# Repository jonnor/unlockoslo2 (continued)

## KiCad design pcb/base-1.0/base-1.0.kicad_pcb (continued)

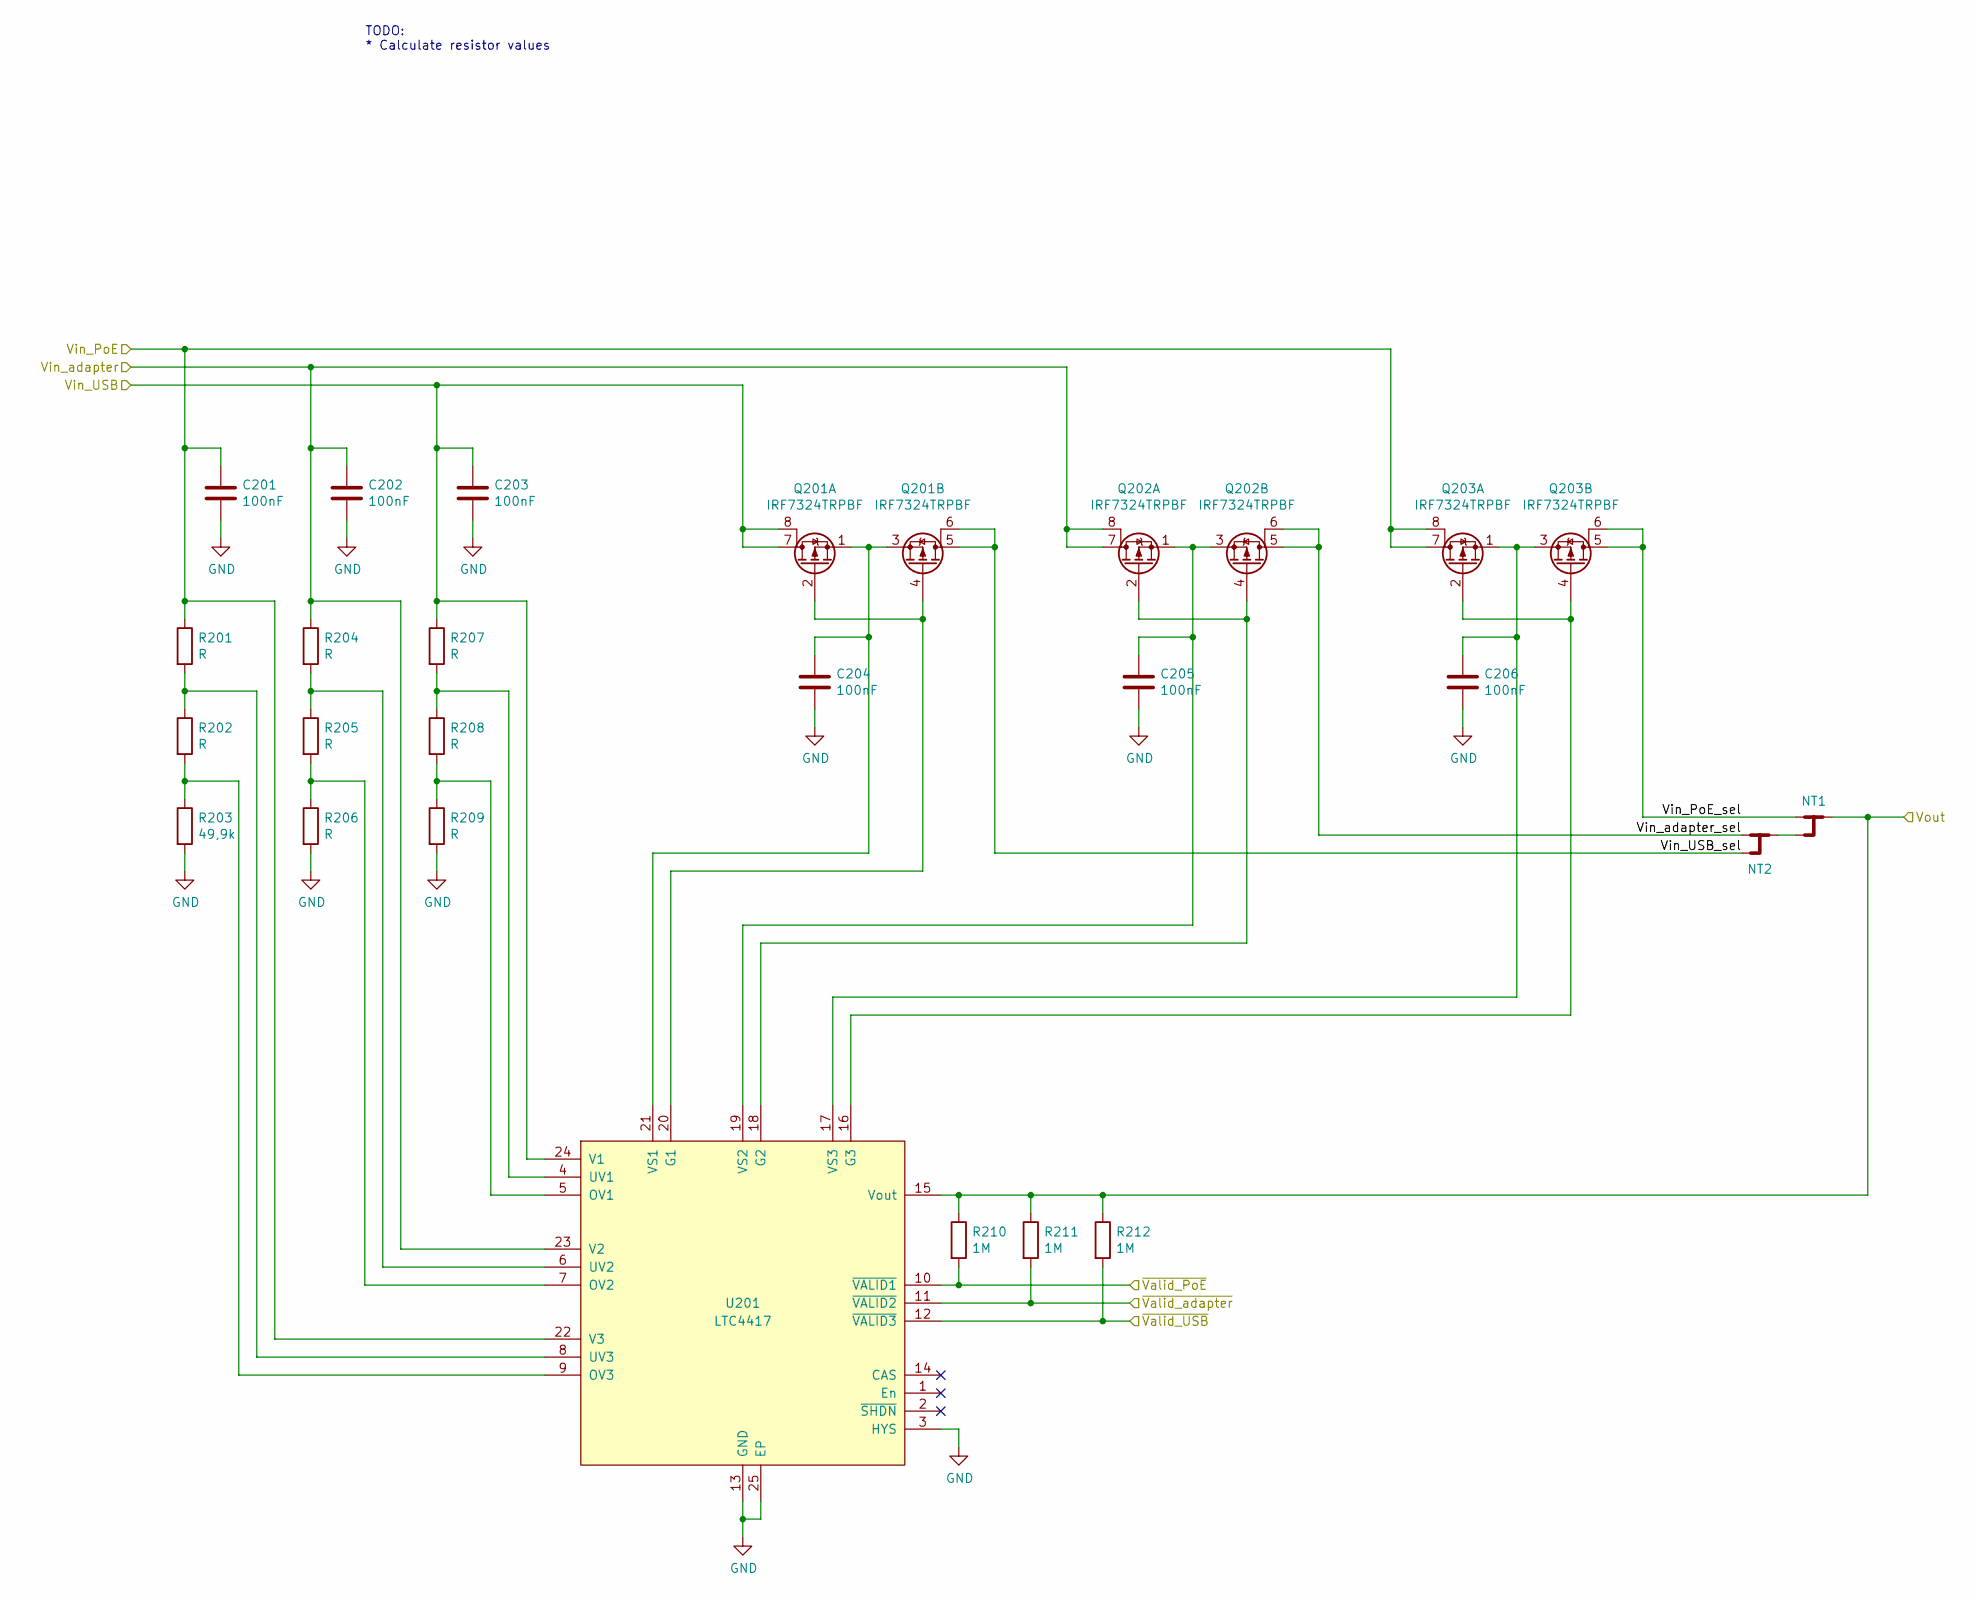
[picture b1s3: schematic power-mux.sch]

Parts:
C201, C202, C203, C204, C205, C206: 100nF; CAPC_1005x015; mpn CL05B104KO5NNNC
NT1, NT2: Net-Tie_3; NetTie-3_SMD_Pad0.5mm_132
Q201, Q202, Q203: IRF7324TRPBF; PowerIntegrations_SO-8; mpn IRF7324TRPBF
R201, R202, R204, R205, R206, R207, R208, R209: R; RESC_1005x015
R203: 49,9k; RESC_1005x015
R210, R211, R212: 1M; RESC_1005x015
U201: LTC4417; QFN-24-1EP_4x4mm_P0.5mm_EP2.6x2.6mm_ThermalVias

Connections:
/Power mux/Vin_PoE: C201.1, Q203.7 (D), Q203.8 (D), R201.1, U201.22 (V3); also elsewhere on the board
/Power mux/Vin_PoE_sel: NT1.1, Q203.5 (D), Q203.6 (D)
/Power mux/Vin_USB: C203.1, Q201.7 (D), Q201.8 (D), R207.1, U201.24 (V1); also elsewhere on the board
/Power mux/Vin_USB_sel: NT2.3, Q201.5 (D), Q201.6 (D)
/Power mux/Vin_adapter: C202.1, Q202.7 (D), Q202.8 (D), R204.1, U201.23 (V2); also elsewhere on the board
/Power mux/Vin_adapter_sel: NT2.1, Q202.5 (D), Q202.6 (D)
/Power mux/~Valid_PoE: R210.2, U201.10 (~VALID1)
/Power mux/~Valid_USB: R212.2, U201.12 (~VALID3)
/Power mux/~Valid_adapter: R211.2, U201.11 (~VALID2)
GND: C201.2, C202.2, C203.2, C204.2, C205.2, C206.2, R203.2, R206.2, R209.2, U201.3 (HYS), U201.13 (GND), U201.25 (EP); also elsewhere on the board
unnamed: C204.1, Q201.1 (S), Q201.3 (S), U201.21 (VS1)
unnamed: C205.1, Q202.1 (S), Q202.3 (S), U201.19 (VS2)
unnamed: C206.1, Q203.1 (S), Q203.3 (S), U201.17 (VS3)
unnamed: NT1.3, NT2.2
unnamed: Q201.2 (G), Q201.4 (G), U201.20 (G1)
unnamed: Q202.2 (G), Q202.4 (G), U201.18 (G2)
unnamed: Q203.2 (G), Q203.4 (G), U201.16 (G3)
unnamed: R201.2, R202.1, U201.8 (UV3)
unnamed: R202.2, R203.1, U201.9 (OV3)
unnamed: R204.2, R205.1, U201.6 (UV2)
unnamed: R205.2, R206.1, U201.7 (OV2)
unnamed: R207.2, R208.1, U201.4 (UV1)
unnamed: R208.2, R209.1, U201.5 (OV1)
Vin: NT1.2, R210.1, R211.1, R212.1, U201.15 (Vout); also elsewhere on the board

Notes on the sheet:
TODO: * Calculate resistor values

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
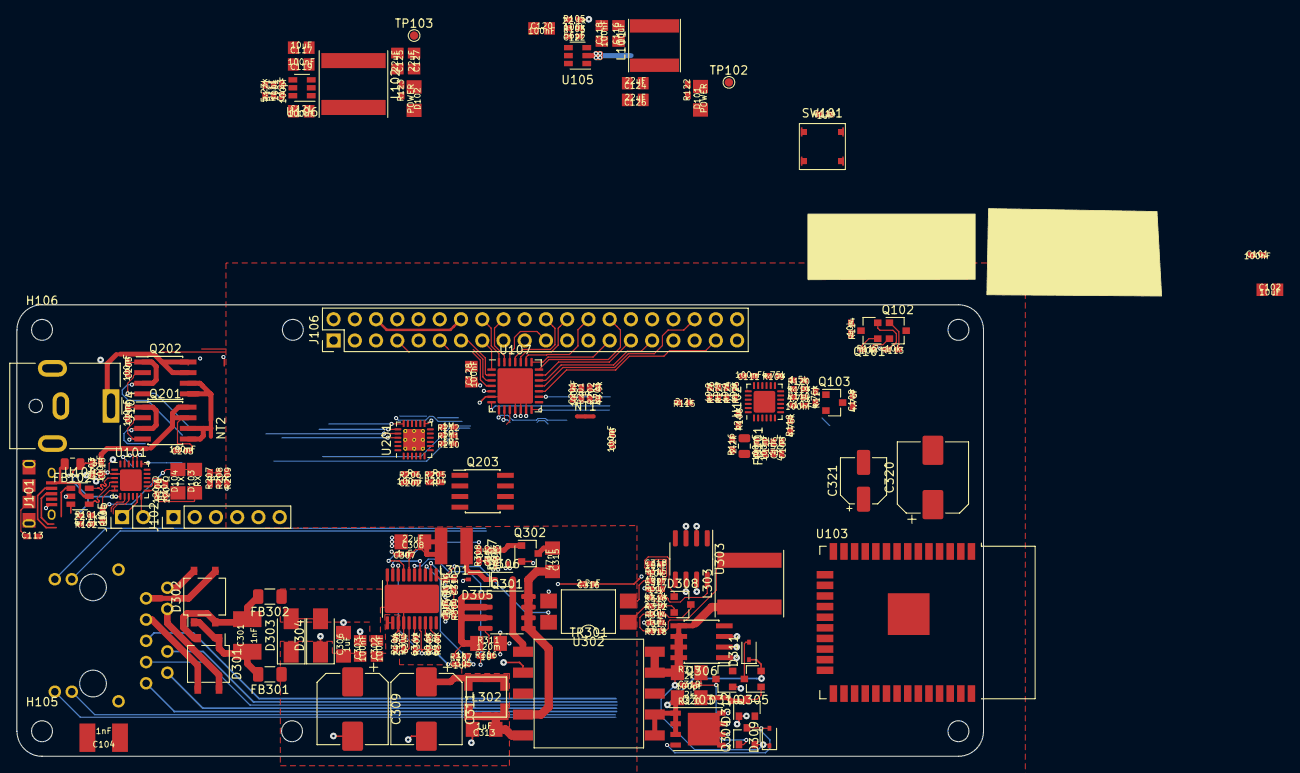
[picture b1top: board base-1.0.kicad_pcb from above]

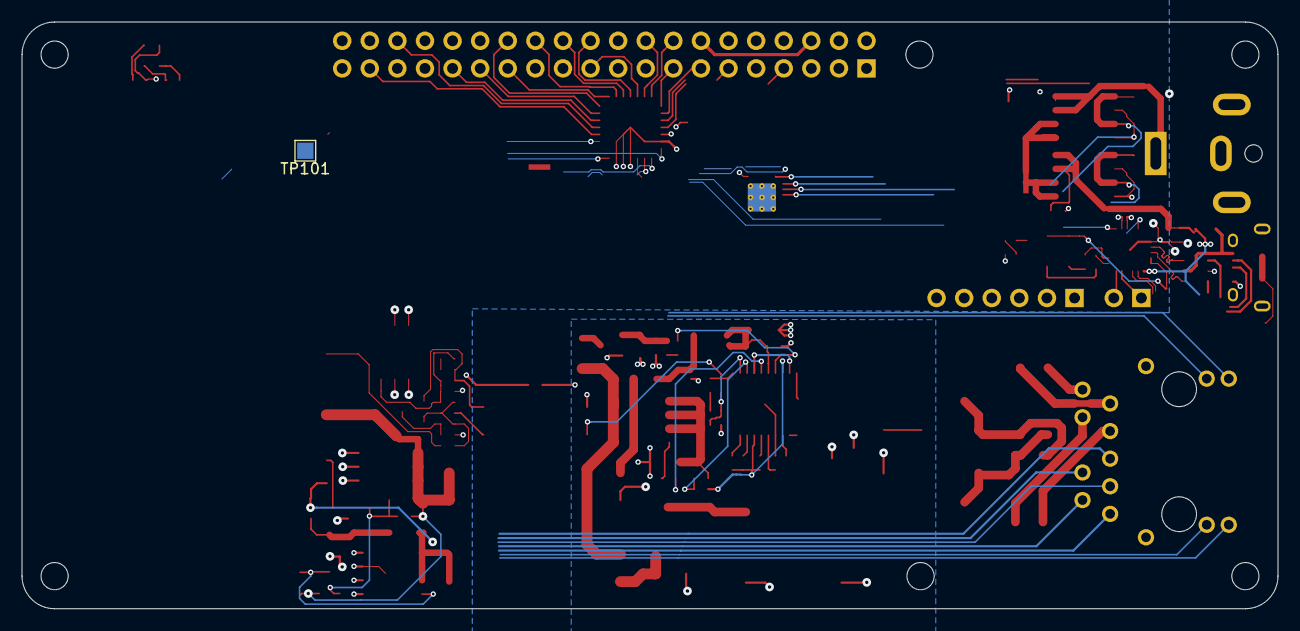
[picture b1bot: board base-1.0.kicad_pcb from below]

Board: 4 copper layers, 115.6 x 54.0 mm, 184 parts (3 on the bottom side), 154 nets.

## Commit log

2019-05-21 TODO
2019-05-27 o Replacing footprints with IPC footprints.
2019-05-27 o Starting on PCB. Using RPI outline for now.
2019-05-27 o Better symbol for BC817, Q101 and Q102. o Adding footprint for jack, J104.
2019-05-27 o Adjusting text size from 60 to 50 mil for imported DC/DC schematic.
2019-05-27 o More values.
2019-05-27 o Selecting parts.
2019-05-27 o Trying to fix bad symbols for the TPS54202 designs.
2019-05-27 o Cleaning up base-1.0.sch, removing extra 'AR Path' lines.
2019-05-27 o More part numbers.
2019-05-28 o Finding more components. o Refreshing generated files.
2019-05-28 o Selecting more parts, fixing footprints.
2019-05-28 o Improving footprints.
2019-05-30 o More footprints and mpns.
2019-05-30 o Adding IO extender for RPI header. o Adding mounting holes in schematic and PCB. o Fixing bad footprint: Capacitor_SMD:CP_Elec_8x10.2 => Capacitor_SMD:CP_Elec_8x10.
2019-05-30 o Starting on PCB. o Fixing minor issues in the schmatic while doing layout.
2019-05-30 o Refreshing IPC footprints to version with 3D models.
2019-05-30 o Placing most of POE parts.
2019-05-31 o Adjusting a couple of symbols. o PoE done for now.
2019-06-04 o Much more PCB work.
2019-06-04 o More PCB work.
2019-06-05 o 4 layers.
2019-06-11 o More MPNs.
2019-06-12 o Refreshing sch.xml.
2019-06-12 o Marking net ties, test points and mounting holes to be skipped from the BOM.
2019-06-12 o More MPNs. o Ignoring DPN parts from BOM. o Changing from TL431D to TL431DBV, has a smaller footprint.
2019-06-12 o Moving all symbols into page.
2019-06-12 firmware: Skeleton for doorsystem logic
2019-06-12 o Removing fixed TODO.
2019-06-12 firmware: Basic unlock logic
2019-06-12 firmware: Program switch logic
2019-06-12 firmware: Opener button logic
2019-06-12 firmware: Door bolt sensor logic
